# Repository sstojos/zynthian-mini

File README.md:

THIS IS AN OLD reposiotry OF ZYNTHIAN MINI !!!

Zyntian MINI is not any more maintained here.

Zynthian MINI is now merged to zynthian-hw repository. You can find latest verison of zynthian mini inside [forked repository of zynthian-hw](https://github.com/sstojos/zynthian-hw) inside MINI_V2 folder.

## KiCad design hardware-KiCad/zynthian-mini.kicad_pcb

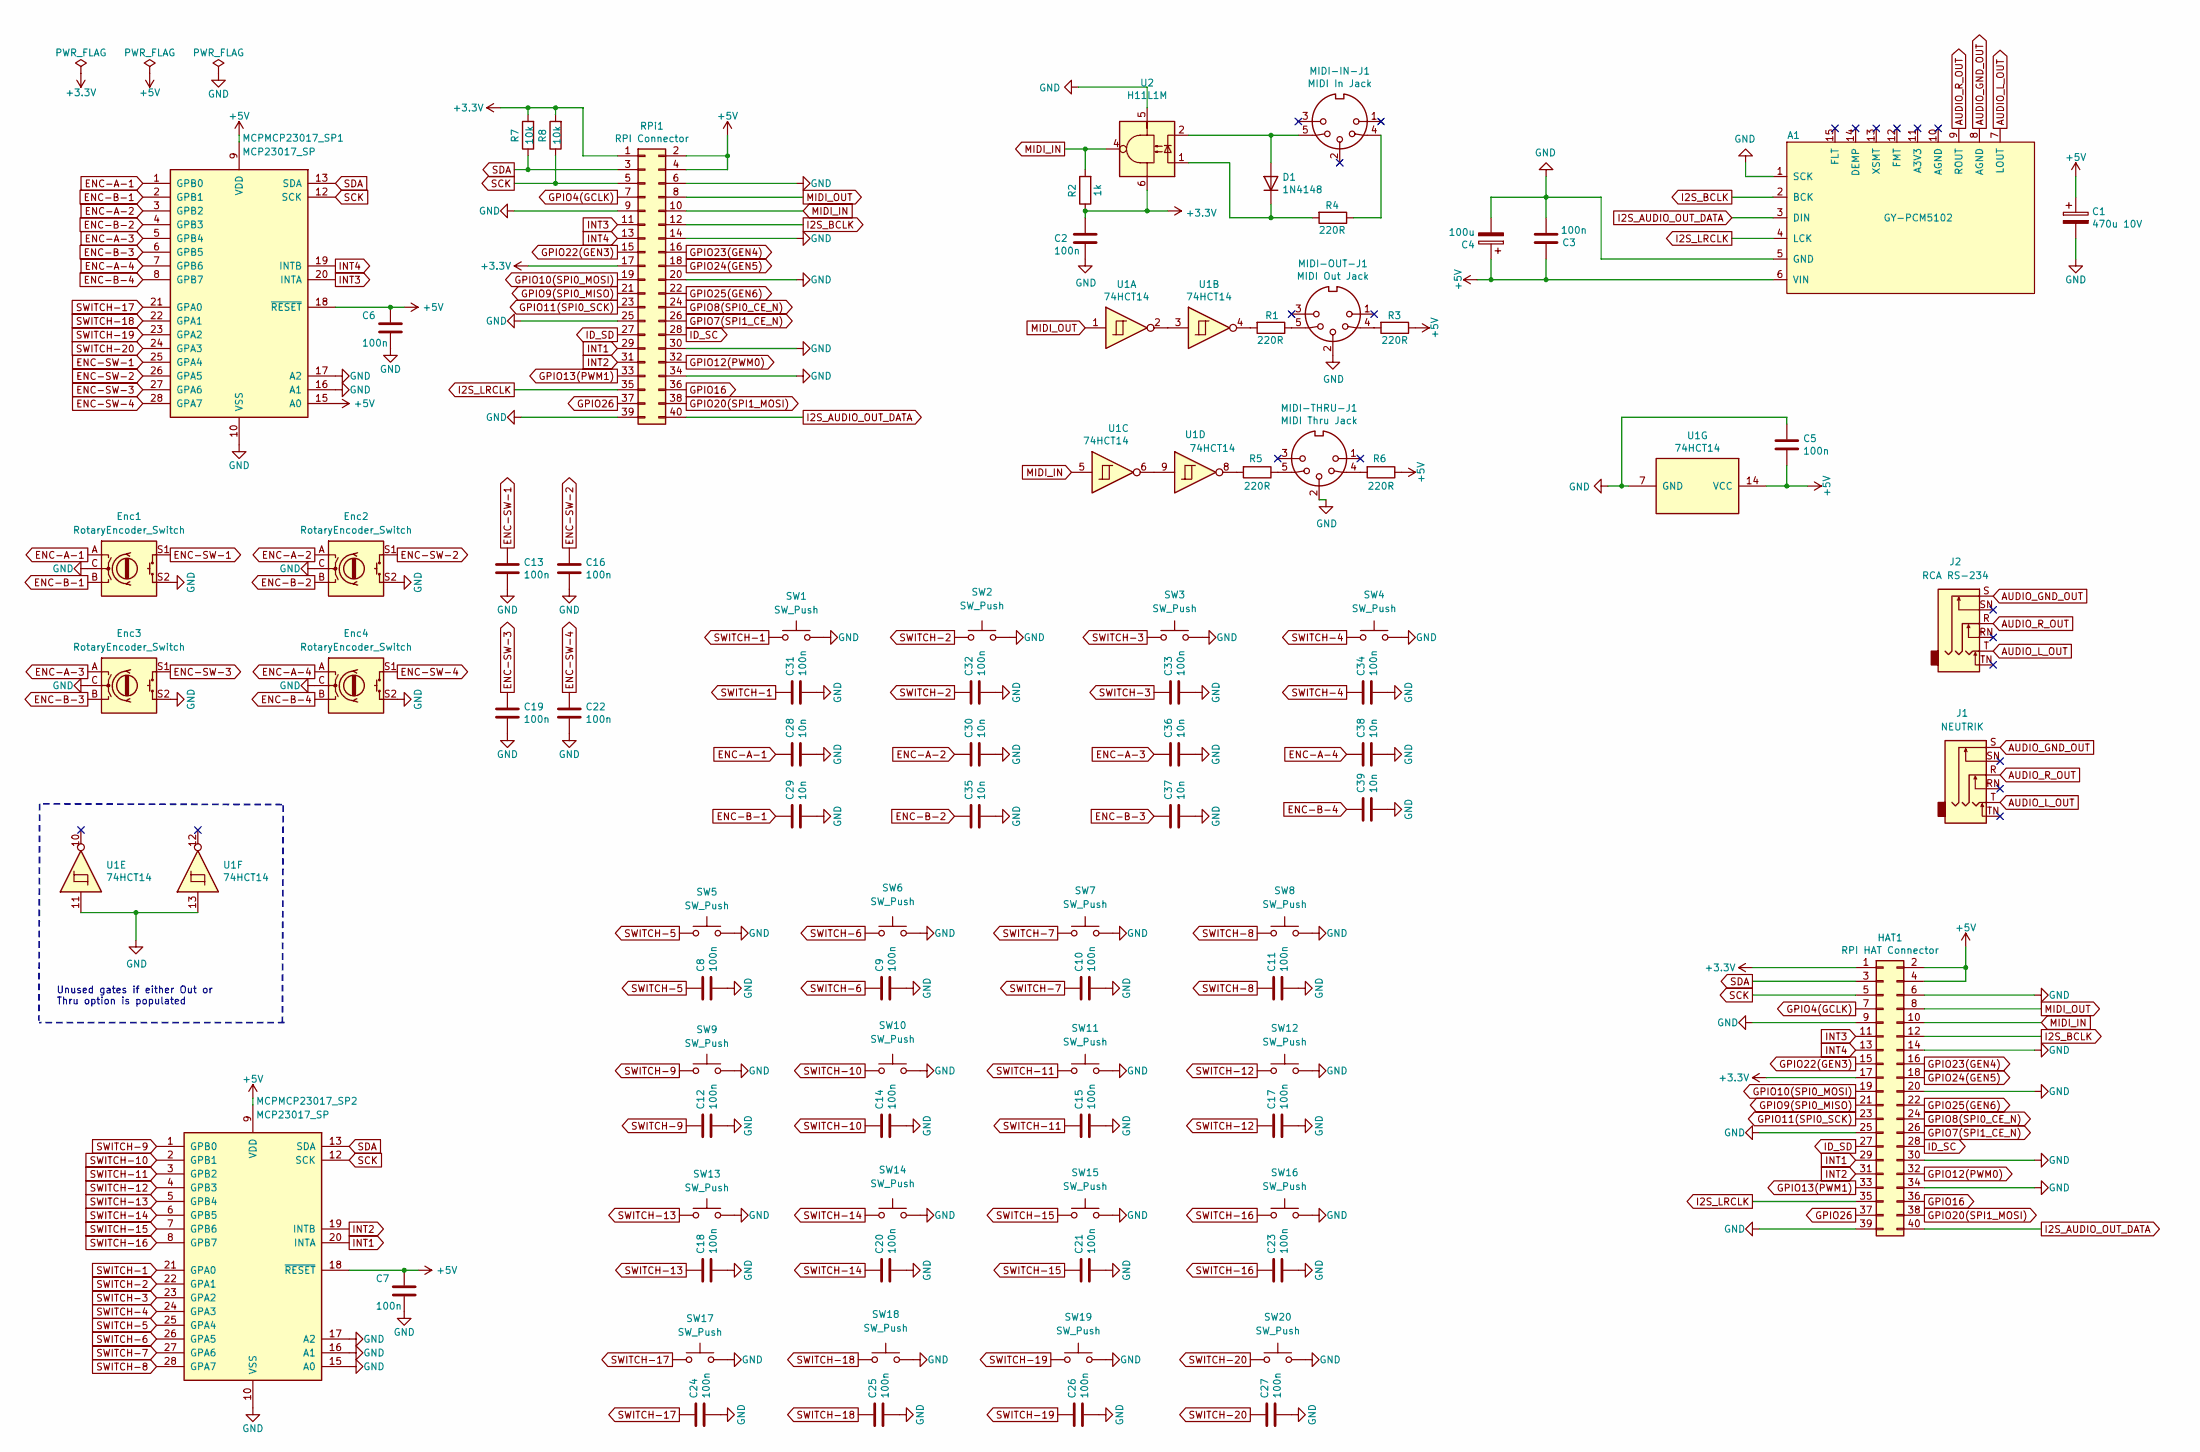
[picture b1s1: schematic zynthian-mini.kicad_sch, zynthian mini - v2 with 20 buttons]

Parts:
A1: GY-PCM5102
C1: 470u 10V; CP_Radial_D8.0mm_P3.50mm
C2, C3, C5, C6, C7: 100n; C_Rect_L7.0mm_W2.0mm_P5.00mm
C4: 100u; CP_Radial_D6.3mm_P2.50mm
C8, C9, C10, C11, C12, C13, C14, C15, C16, C17, C18, C19, C20, C21, C22, C23, C24, C25, C26, C27, C31, C32, C33, C34: 100n; C_Rect_L4.0mm_W2.5mm_P2.50mm
C28, C29, C30, C35, C36, C37, C38, C39: 10n; C_Rect_L4.0mm_W2.5mm_P2.50mm
D1: 1N4148; D_DO-35_SOD27_P7.62mm_Horizontal
Enc1, Enc2, Enc3, Enc4: RotaryEncoder_Switch; RotaryEncoder_Alps_EC12E-Switch_Vertical_H20mm
HAT1: RPI HAT Connector; raspberry pi 4
J1: NEUTRIK; Jack_6.35mm_Neutrik_NMJ6HFD2_Horizontal
J2: RCA RS-234
MCPMCP23017_SP1, MCPMCP23017_SP2: MCP23017_SP; DIP-28_W7.62mm
MIDI-IN-J1: MIDI In Jack; MultiDIN5
MIDI-OUT-J1: MIDI Out Jack; MultiDIN5
MIDI-THRU-J1: MIDI Thru Jack; MultiDIN5
R1, R3, R4, R5, R6: 220R; R_Axial_DIN0207_L6.3mm_D2.5mm_P7.62mm_Horizontal
R2: 1k; R_Axial_DIN0207_L6.3mm_D2.5mm_P7.62mm_Horizontal
R7, R8: 10k; R_Axial_DIN0207_L6.3mm_D2.5mm_P7.62mm_Horizontal
RPi1: RPI Connector; raspberry pi 4 HAT
SW1, SW2, SW3, SW4, SW5, SW6, SW7, SW8, SW9, SW10, SW11, SW12, SW13, SW14, SW15, SW16, SW17, SW18, SW19, SW20: SW_Push; push-button
U1: 74HCT14; DIP-14_W7.62mm
U2: H11L1M; DIP-6_W7.62mm

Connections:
AUDIO_GND_OUT: A1.8 (AGND), J1.S, J2.S
AUDIO_L_OUT: A1.7 (LOUT), J1.T, J2.T
AUDIO_R_OUT: A1.9 (ROUT), J1.R, J2.R
ENC-A-1: C28.1, Enc1.A, MCPMCP23017_SP1.1 (GPB0)
ENC-A-2: C30.1, Enc2.A, MCPMCP23017_SP1.3 (GPB2)
ENC-A-3: C36.1, Enc3.A, MCPMCP23017_SP1.5 (GPB4)
ENC-A-4: C38.1, Enc4.A, MCPMCP23017_SP1.7 (GPB6)
ENC-B-1: C29.1, Enc1.B, MCPMCP23017_SP1.2 (GPB1)
ENC-B-2: C35.1, Enc2.B, MCPMCP23017_SP1.4 (GPB3)
ENC-B-3: C37.1, Enc3.B, MCPMCP23017_SP1.6 (GPB5)
ENC-B-4: C39.1, Enc4.B, MCPMCP23017_SP1.8 (GPB7)
ENC-SW-1: C13.1, Enc1.S1, MCPMCP23017_SP1.25 (GPA4)
ENC-SW-2: C16.1, Enc2.S1, MCPMCP23017_SP1.26 (GPA5)
ENC-SW-3: C19.1, Enc3.S1, MCPMCP23017_SP1.27 (GPA6)
ENC-SW-4: C22.1, Enc4.S1, MCPMCP23017_SP1.28 (GPA7)
GPIO4(GCLK): HAT1.7, RPi1.7
GPIO7(SPI1_CE_N): HAT1.26, RPi1.26
GPIO8(SPI0_CE_N): HAT1.24, RPi1.24
GPIO9(SPI0_MISO): HAT1.21, RPi1.21
GPIO10(SPI0_MOSI): HAT1.19, RPi1.19
GPIO11(SPI0_SCK): HAT1.23, RPi1.23
GPIO12(PWM0): HAT1.32, RPi1.32
GPIO13(PWM1): HAT1.33, RPi1.33
GPIO16: HAT1.36, RPi1.36
GPIO20(SPI1_MOSI): HAT1.38, RPi1.38
GPIO22(GEN3): HAT1.15, RPi1.15
GPIO23(GEN4): HAT1.16, RPi1.16
GPIO24(GEN5): HAT1.18, RPi1.18
GPIO25(GEN6): HAT1.22, RPi1.22
GPIO26: HAT1.37, RPi1.37
I2S_AUDIO_OUT_DATA: A1.3 (DIN), HAT1.40, RPi1.40
I2S_BCLK: A1.2 (BCK), HAT1.12, RPi1.12
I2S_LRCLK: A1.4 (LCK), HAT1.35, RPi1.35
ID_SC: HAT1.28, RPi1.28
ID_SD: HAT1.27, RPi1.27
INT1: HAT1.29, MCPMCP23017_SP2.20 (INTA), RPi1.29
INT2: HAT1.31, MCPMCP23017_SP2.19 (INTB), RPi1.31
INT3: HAT1.11, MCPMCP23017_SP1.20 (INTA), RPi1.11
INT4: HAT1.13, MCPMCP23017_SP1.19 (INTB), RPi1.13
MIDI_IN: HAT1.10, R2.2, RPi1.10, U1.5, U2.4
MIDI_OUT: HAT1.8, RPi1.8, U1.1
unnamed: D1.2 (A), MIDI-IN-J1.5, U2.2
unnamed: D1.1 (K), R4.2, U2.1
unnamed: MIDI-IN-J1.4, R4.1
unnamed: MIDI-OUT-J1.4, R3.2
unnamed: MIDI-OUT-J1.5, R1.1
unnamed: MIDI-THRU-J1.4, R6.2
unnamed: MIDI-THRU-J1.5, R5.1
unnamed: R1.2, U1.4
unnamed: R5.2, U1.8
unnamed: U1.2, U1.3
unnamed: U1.6, U1.9
SCK: HAT1.5, MCPMCP23017_SP1.12 (SCK), MCPMCP23017_SP2.12 (SCK), R8.1, RPi1.5
SDA: HAT1.3, MCPMCP23017_SP1.13 (SDA), MCPMCP23017_SP2.13 (SDA), R7.1, RPi1.3
SWITCH-1: C31.1, MCPMCP23017_SP2.21 (GPA0), SW1.1
SWITCH-2: C32.1, MCPMCP23017_SP2.22 (GPA1), SW2.1
SWITCH-3: C33.1, MCPMCP23017_SP2.23 (GPA2), SW3.1
SWITCH-4: C34.1, MCPMCP23017_SP2.24 (GPA3), SW4.1
SWITCH-5: C8.1, MCPMCP23017_SP2.25 (GPA4), SW5.1
SWITCH-6: C9.1, MCPMCP23017_SP2.26 (GPA5), SW6.1
SWITCH-7: C10.1, MCPMCP23017_SP2.27 (GPA6), SW7.1
SWITCH-8: C11.1, MCPMCP23017_SP2.28 (GPA7), SW8.1
SWITCH-9: C12.1, MCPMCP23017_SP2.1 (GPB0), SW9.1
SWITCH-10: C14.1, MCPMCP23017_SP2.2 (GPB1), SW10.1
SWITCH-11: C15.1, MCPMCP23017_SP2.3 (GPB2), SW11.1
SWITCH-12: C17.1, MCPMCP23017_SP2.4 (GPB3), SW12.1
SWITCH-13: C18.1, MCPMCP23017_SP2.5 (GPB4), SW13.1
SWITCH-14: C20.1, MCPMCP23017_SP2.6 (GPB5), SW14.1
SWITCH-15: C21.1, MCPMCP23017_SP2.7 (GPB6), SW15.1
SWITCH-16: C23.1, MCPMCP23017_SP2.8 (GPB7), SW16.1
SWITCH-17: C24.1, MCPMCP23017_SP1.21 (GPA0), SW17.1
SWITCH-18: C25.1, MCPMCP23017_SP1.22 (GPA1), SW18.1
SWITCH-19: C26.1, MCPMCP23017_SP1.23 (GPA2), SW19.1
SWITCH-20: C27.1, MCPMCP23017_SP1.24 (GPA3), SW20.1

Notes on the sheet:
Unused gates if either Out or Thru option is populated

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
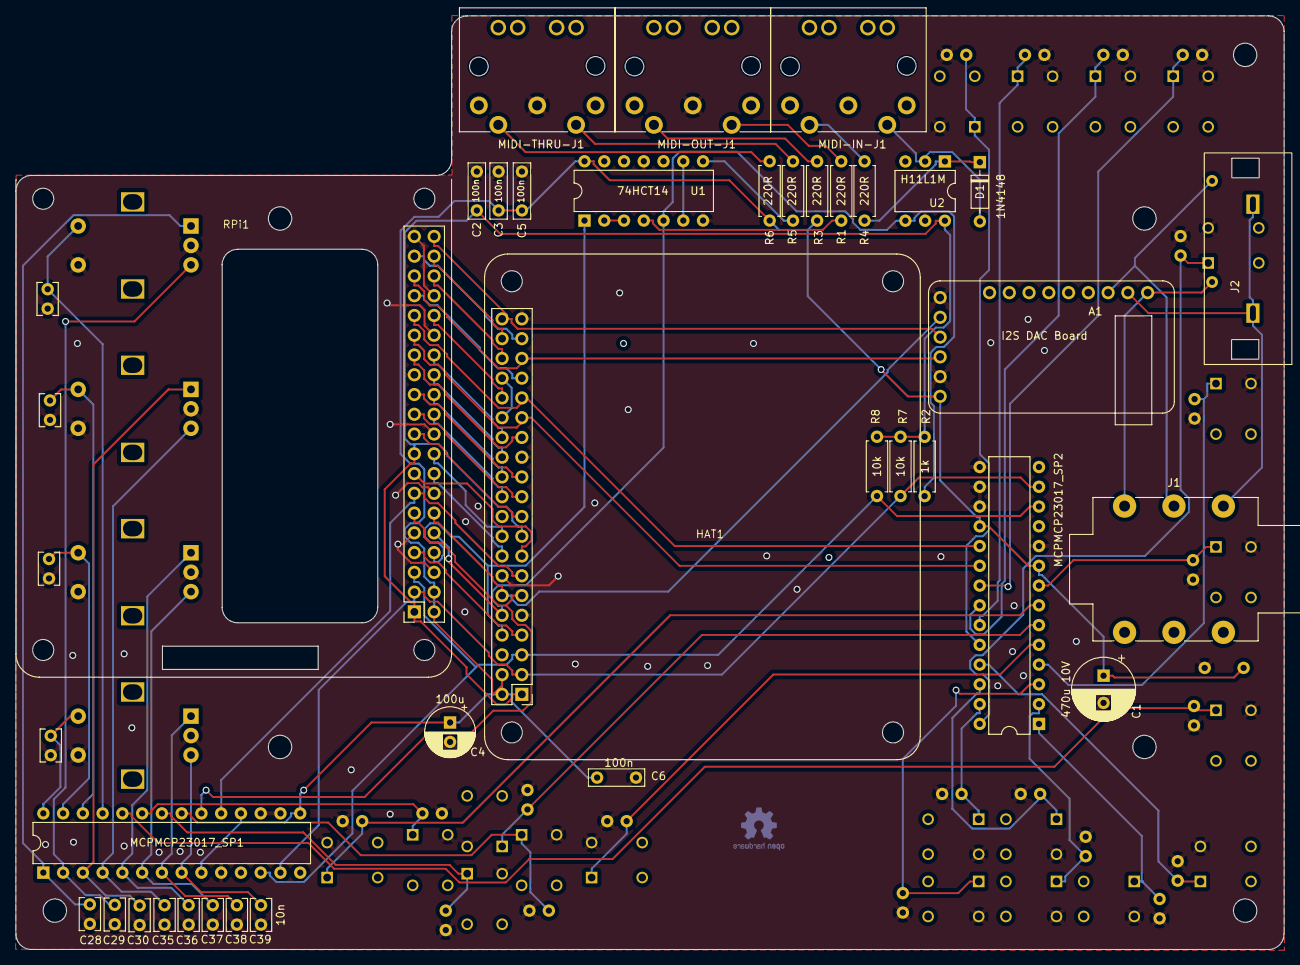
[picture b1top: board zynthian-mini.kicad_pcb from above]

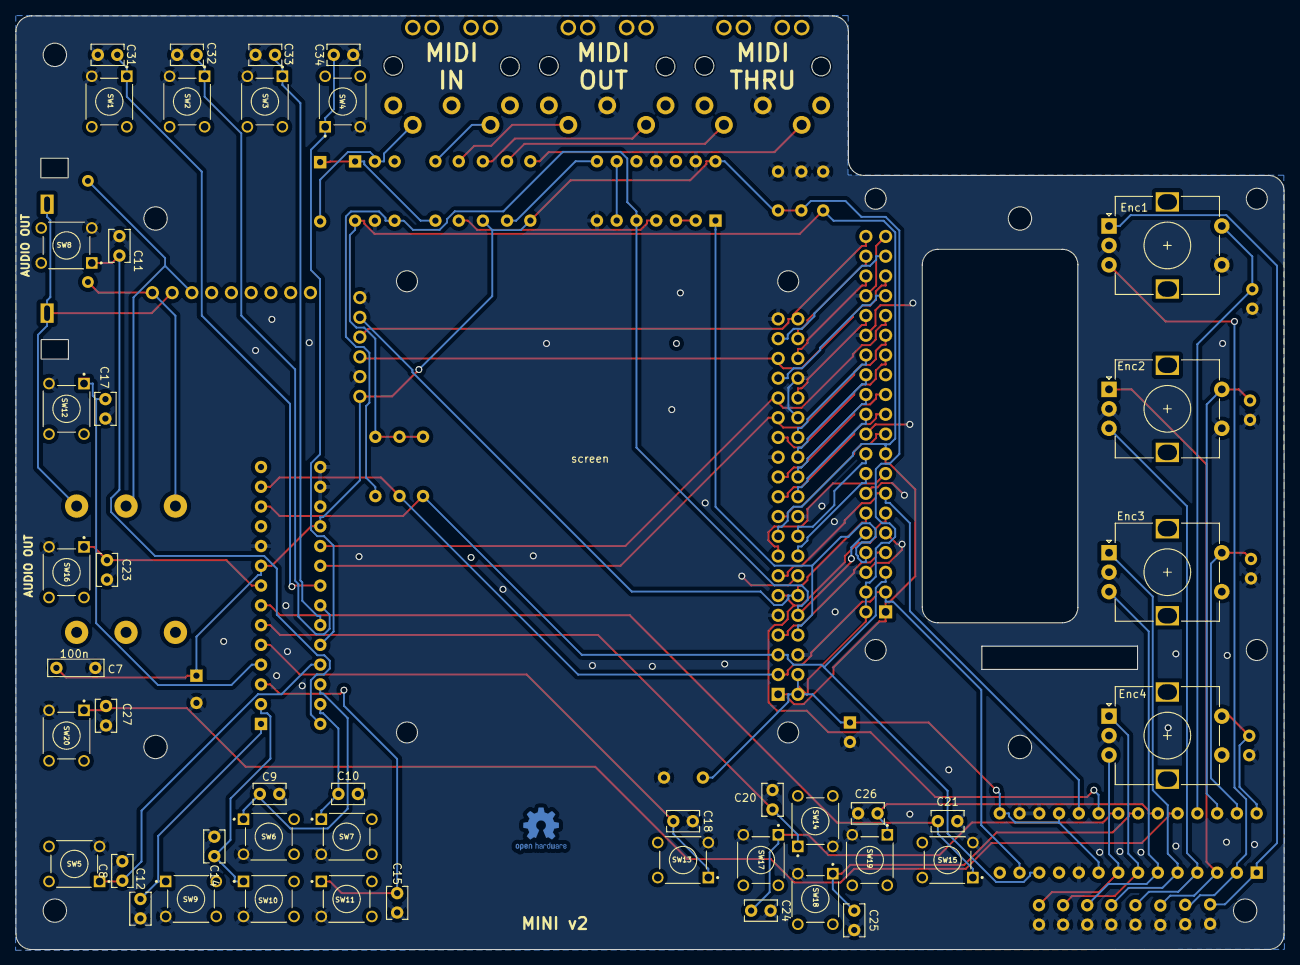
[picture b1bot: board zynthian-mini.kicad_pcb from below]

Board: 2 copper layers, 163.0 x 120.0 mm, 85 parts (45 on the bottom side), 77 nets.

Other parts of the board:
screen: aliexpress 5 inch screen

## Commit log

2024-03-20 first release
2024-03-24 migration to KiCad 8.0
2024-03-31 second release
2024-04-02 small change
2024-04-02 Revert "first release"
    This reverts commit 41a2be58bfaad8c4c6ee26f01870b28e54c5dbaa.
2024-04-02 Revert "small change"
    This reverts commit bf56d786448eb0d1813ac91ff1c23d49941d9939.
2024-04-02 Reapply "first release"
    This reverts commit b86c050a3e52f940a0b2b15bb35b2e8c69fdf6d7.
2024-04-02 Revert "second release"
    This reverts commit bd4749c021c126e3d20c8e6cac66855f5c73ca6a.
2024-04-02 removed kicad lock file
2024-04-02 removed lock file
2024-04-02 Reapply "second release"
    This reverts commit ecf339a646dc757298e7c83805a64127a07718a0.
2024-04-03 PCB board edge chnage
2024-04-03 first button layout try
2024-04-03 work on PCB switches and CAD
2024-04-04 first usable v2-20-buttons version
2024-04-06 making space for rpi4
2024-04-08 first workable solution for v2 20 pins
2024-04-09 added RCA, Neutrik and HAT connector
2024-04-09 added PCB back with rpi image
2024-04-09 added posts for PCB inside the case
2024-04-14 reverted back to v1-beta version for saving it into its own branch
2024-04-15 case almost completed - few fixes required
2024-04-15 enlarged case for 0.6mm - both sides - for the easier PCB fit
2024-04-19 added CAD files
2024-04-23 v2 assembling photos and latest 3d design
2024-04-26 CAD design final
2024-04-30 added encoder de bouncing caps
2024-04-30 added configuration screenshots
2024-04-30 assembly photo updates
2024-05-01 assembling images sorted
2024-05-01 another assembling images additions / changes
2024-05-01 images resize
2024-05-01 Update README.md to suite MINI V2
2024-05-01 Updated to fix broker links README.md
2024-05-01 finished case design and exported all parts in stl
2024-05-01 removed freecad backup file
2024-05-02 final case adjustments
2024-05-03 small changes to silkscreen component info
2024-05-03 added orcaslicer project and fixed bottom part openings
2024-05-03 bottom part timelapse
2024-05-04 assembling photos
